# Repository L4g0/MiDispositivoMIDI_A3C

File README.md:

# BanaNut Electronics
Hi! We are BanaNut Electronics and we develop software and hardware for Arduino with educational purposes. Feel free to visit us in out social networks:
* Instagram: https://www.instagram.com/bananutelectronics
* Twitter: https://twitter.com/bn_electronics
* Facebook: https://www.facebook.com/bananutelectronics
* Tindie: https://www.tindie.com

# MiDispositivoMIDI_A3C
We are proud to present the MiDispositivoMIDI revA3C ([what is that?](https://github.com/bananutelectronics/MiDispositivoMIDI_A3C/wiki), which is the latest version we have out in the market. You can buy it in our webpage or in tindie. In this repository you will find documentation about the controller and code. If you know how to code and you want to colaborate with the project, feel free to do it. If you don't, here you will find a bunch of codes that you just will need to upload to your controller, simple as that.

# Important
You will need the following libraries to make the code work: MIDI USB and Adafruit NeoPixel
* https://github.com/arduino-libraries/MIDIUSB
* https://github.com/adafruit/Adafruit_NeoPixel

We also recommend using the Arduino Sketch to make the programming. Remember to select "Arduino Leonardo" as target board.

# Media
* https://www.youtube.com/watch?v=3QnzLwpbpRE&t
* https://www.youtube.com/watch?v=8WFfShg-0Dk
* https://www.youtube.com/watch?v=2y8fhmTmedI
* https://www.youtube.com/watch?v=TsuVpFoLFyI

# General information
* MiDispositivoMIDI is the latest version of our controller.
* It can act as any other MIDI device. There is no need to convert from serial to MIDI.
* Have 16 pad buttons in a 4x4 matrix.
* Have 2 lateral buttons.
* Have RGB leds with 256 levels of intensity of each color.
* Micro USB conection.
* Dimensions of 10x10 cm.

# Documentation
Check the wiki section for further information.

# Hardware License
<br /><span xmlns:dct="http://purl.org/dc/terms/" property="dct:title">MiDispositivoMIDI</span> by <a xmlns:cc="http://creativecommons.org/ns#" href="www.bananutelectronics.com" property="cc:attributionName" rel="cc:attributionURL">Alvaro Lopez & Pablo de Miguel Morales</a> is licensed under a <a rel="license" href="http://creativecommons.org/licenses/by-nc-sa/4.0/">Creative Commons Attribution-NonCommercial-ShareAlike 4.0 International License</a>.<br />

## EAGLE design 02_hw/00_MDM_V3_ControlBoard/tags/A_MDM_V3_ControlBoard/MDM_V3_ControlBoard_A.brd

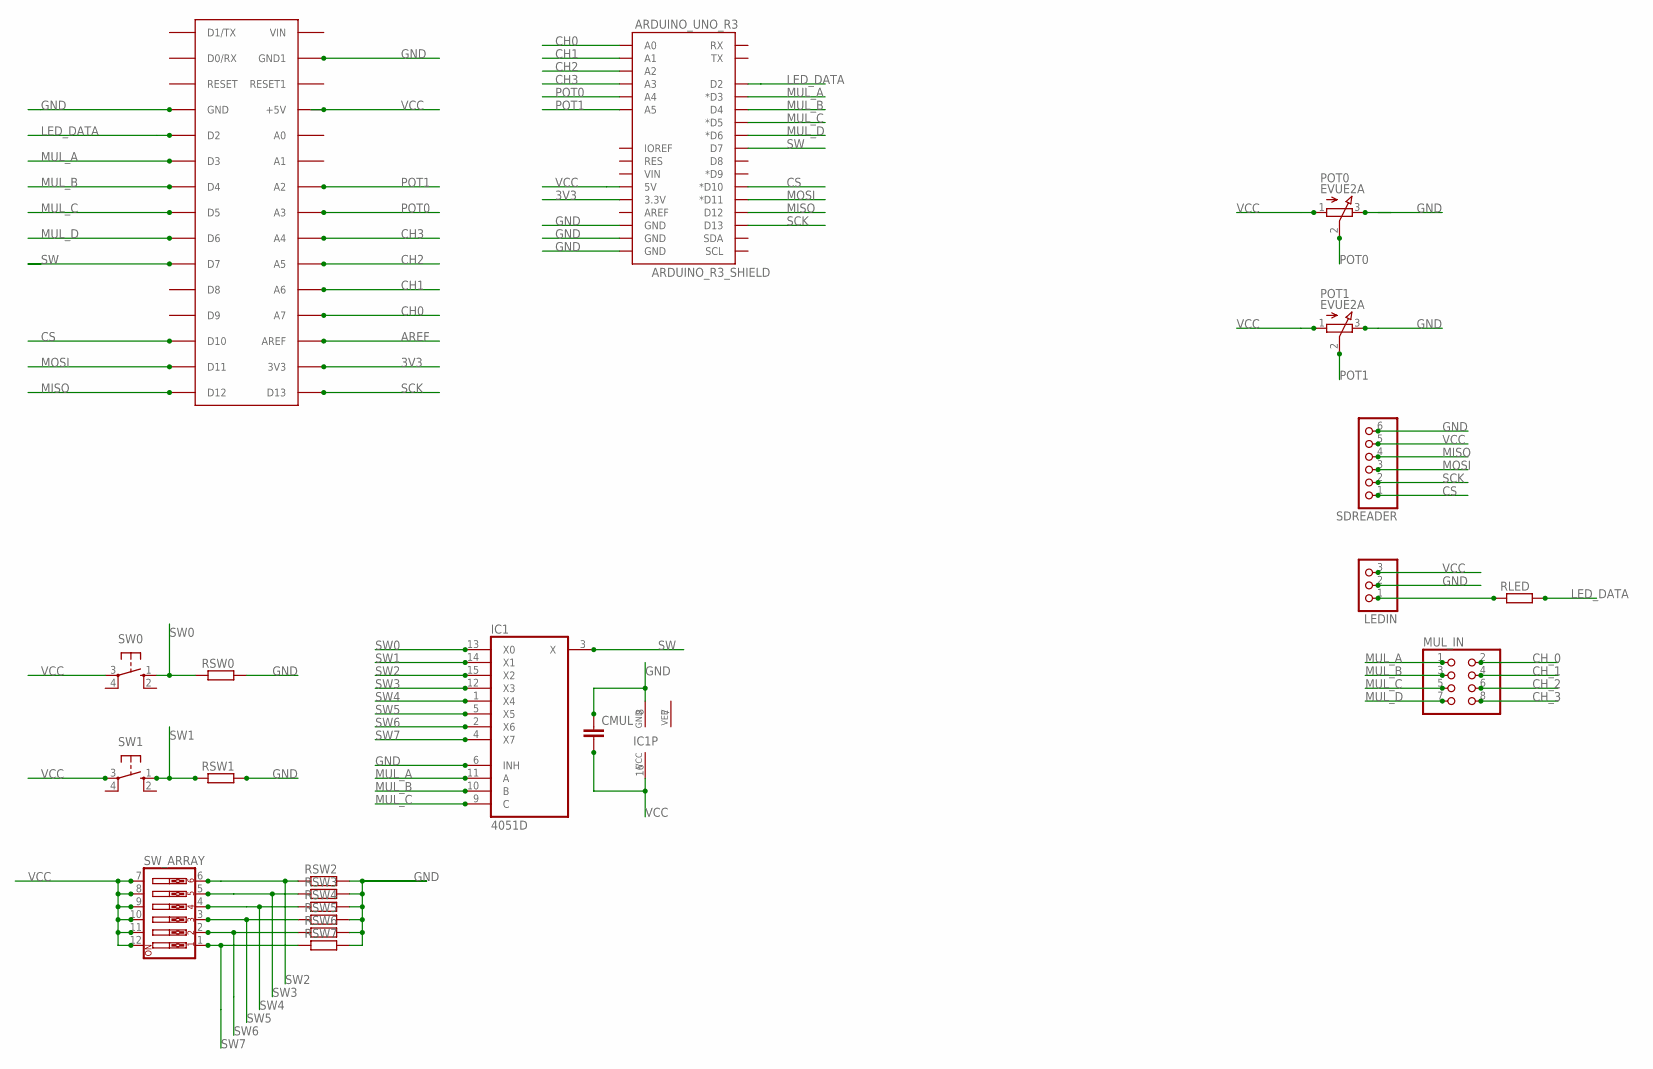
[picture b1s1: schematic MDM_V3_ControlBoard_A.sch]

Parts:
ARDUINO_NANO: ARDUINONANO; PDIP-32
ARDUINO_UNO_R3: ARDUINO_R3_SHIELD; UNO_R3_SHIELD
CMUL: C-EUC1206; C1206
IC1: 4051D; SO16
LEDIN: PINHD-1X3; 1X03
MUL_IN: PINHD-2X4; 2X04
POT0, POT1: EVUE2A; EVUE
RLED: R-EU_M1206; M1206
RSW0, RSW1, RSW2, RSW3, RSW4, RSW5, RSW6, RSW7: R-EU_M1206; M1206
SDREADER: PINHD-1X6; 1X06
SW0, SW1: 10-XX; B3F-10XX
SW_ARRAY: SW_DIP-6; EDG-06

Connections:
3V3: ARDUINO_NANO.3V3, ARDUINO_UNO_R3.3.3V
AREF: ARDUINO_NANO.AREF
CH0: ARDUINO_NANO.A7, ARDUINO_UNO_R3.A0
CH1: ARDUINO_NANO.A6, ARDUINO_UNO_R3.A1
CH2: ARDUINO_NANO.A5, ARDUINO_UNO_R3.A2
CH3: ARDUINO_NANO.A4, ARDUINO_UNO_R3.A3
CH_0: MUL_IN.2
CH_1: MUL_IN.4
CH_2: MUL_IN.6
CH_3: MUL_IN.8
CS: ARDUINO_NANO.D10, ARDUINO_UNO_R3.D10 (*D10), SDREADER.1
GND: ARDUINO_NANO.GND, ARDUINO_NANO.GND1, ARDUINO_UNO_R3.GND@0 (GND), ARDUINO_UNO_R3.GND@1 (GND), ARDUINO_UNO_R3.GND@2 (GND), CMUL.1, IC1.6 (INH), IC1.8 (GND), LEDIN.2, POT0.3 (E), POT1.3 (E), RSW0.2, RSW1.2, RSW2.2, RSW3.2, RSW4.2, RSW5.2, RSW6.2, RSW7.2, SDREADER.6
LED_DATA: ARDUINO_NANO.D2, ARDUINO_UNO_R3.D2, RLED.2
MISO: ARDUINO_NANO.D12, ARDUINO_UNO_R3.D12, SDREADER.4
MOSI: ARDUINO_NANO.D11, ARDUINO_UNO_R3.D11 (*D11), SDREADER.3
MUL_A: ARDUINO_NANO.D3, ARDUINO_UNO_R3.D3 (*D3), IC1.11 (A), MUL_IN.1
MUL_B: ARDUINO_NANO.D4, ARDUINO_UNO_R3.D4, IC1.10 (B), MUL_IN.3
MUL_C: ARDUINO_NANO.D5, ARDUINO_UNO_R3.D5 (*D5), IC1.9 (C), MUL_IN.5
MUL_D: ARDUINO_NANO.D6, ARDUINO_UNO_R3.D6 (*D6), MUL_IN.7
unnamed: LEDIN.1, RLED.1
POT0: ARDUINO_NANO.A3, ARDUINO_UNO_R3.A4, POT0.2 (S)
POT1: ARDUINO_NANO.A2, ARDUINO_UNO_R3.A5, POT1.2 (S)
SCK: ARDUINO_NANO.D13, ARDUINO_UNO_R3.D13, SDREADER.2
SW: ARDUINO_NANO.D7, ARDUINO_UNO_R3.D7, IC1.3 (X)
SW0: IC1.13 (X0), RSW0.1, SW0.1 (S)
SW1: IC1.14 (X1), RSW1.1, SW1.1 (S)
SW2: IC1.15 (X2), RSW2.1, SW_ARRAY.6
SW3: IC1.12 (X3), RSW3.1, SW_ARRAY.5
SW4: IC1.1 (X4), RSW4.1, SW_ARRAY.4
SW5: IC1.5 (X5), RSW5.1, SW_ARRAY.3
SW6: IC1.2 (X6), RSW6.1, SW_ARRAY.2
SW7: IC1.4 (X7), RSW7.1, SW_ARRAY.1
VCC: ARDUINO_NANO.+5V, ARDUINO_UNO_R3.5V, CMUL.2, IC1.16 (VCC), LEDIN.3, POT0.1 (A), POT1.1 (A), SDREADER.5, SW0.3, SW1.3, SW_ARRAY.7, SW_ARRAY.8, SW_ARRAY.9, SW_ARRAY.10, SW_ARRAY.11, SW_ARRAY.12
VEE: IC1.7 (VEE)

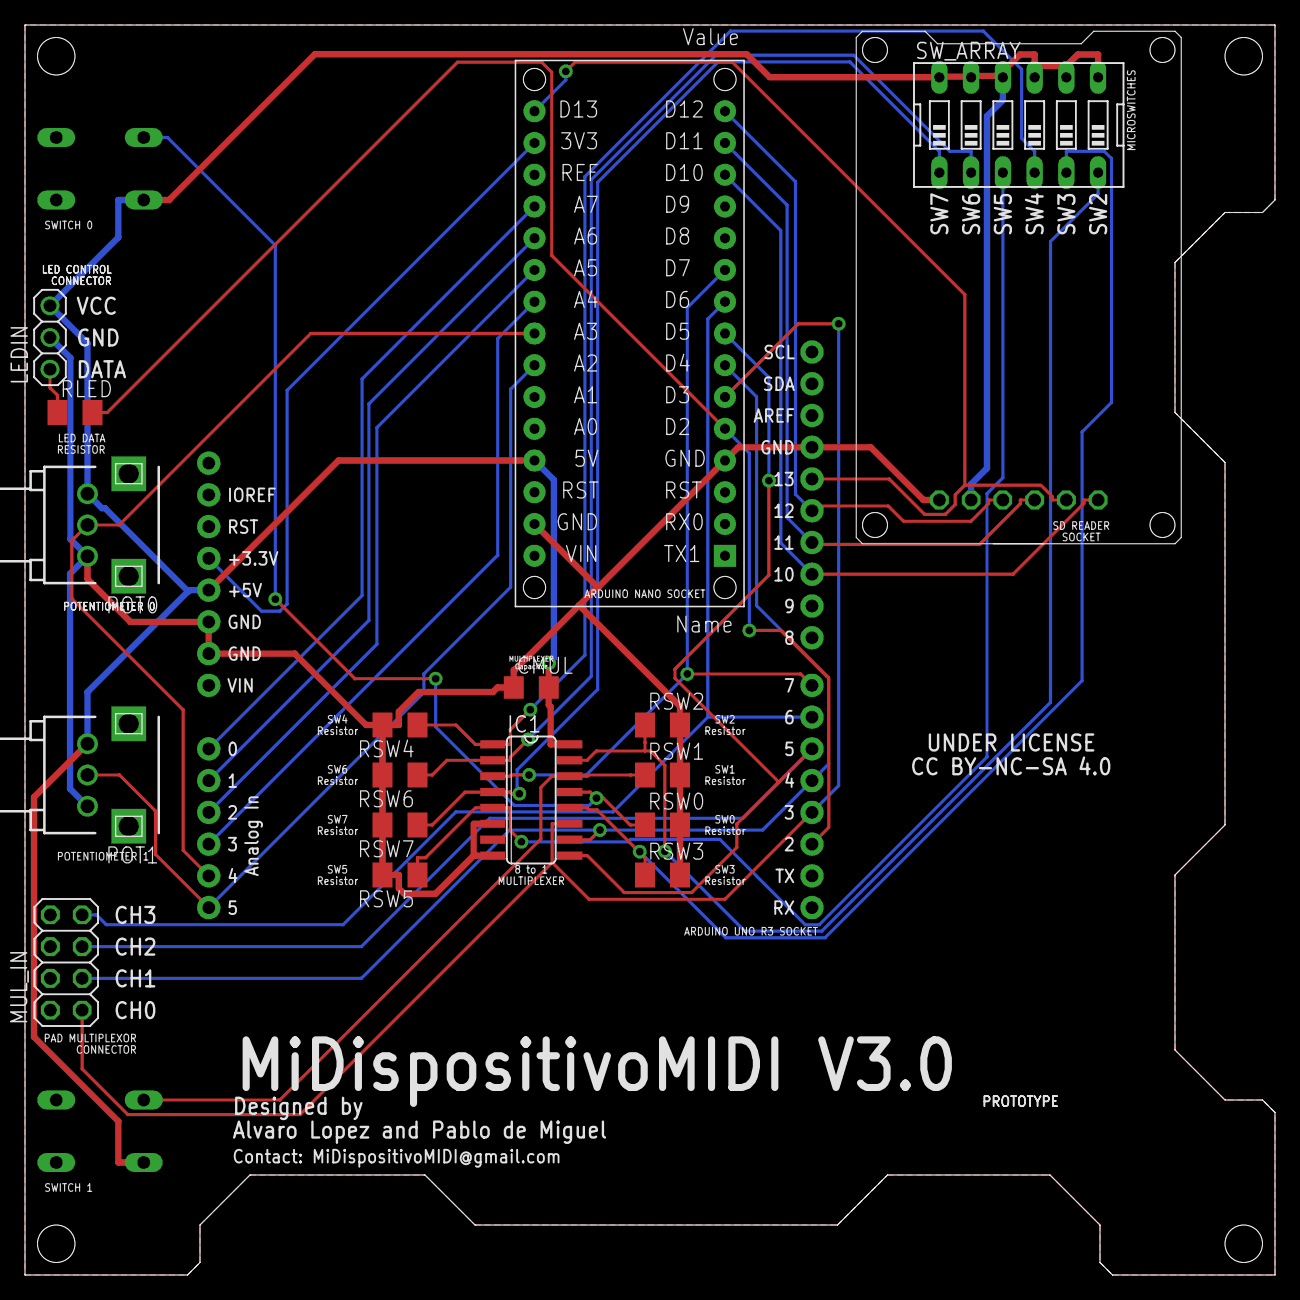
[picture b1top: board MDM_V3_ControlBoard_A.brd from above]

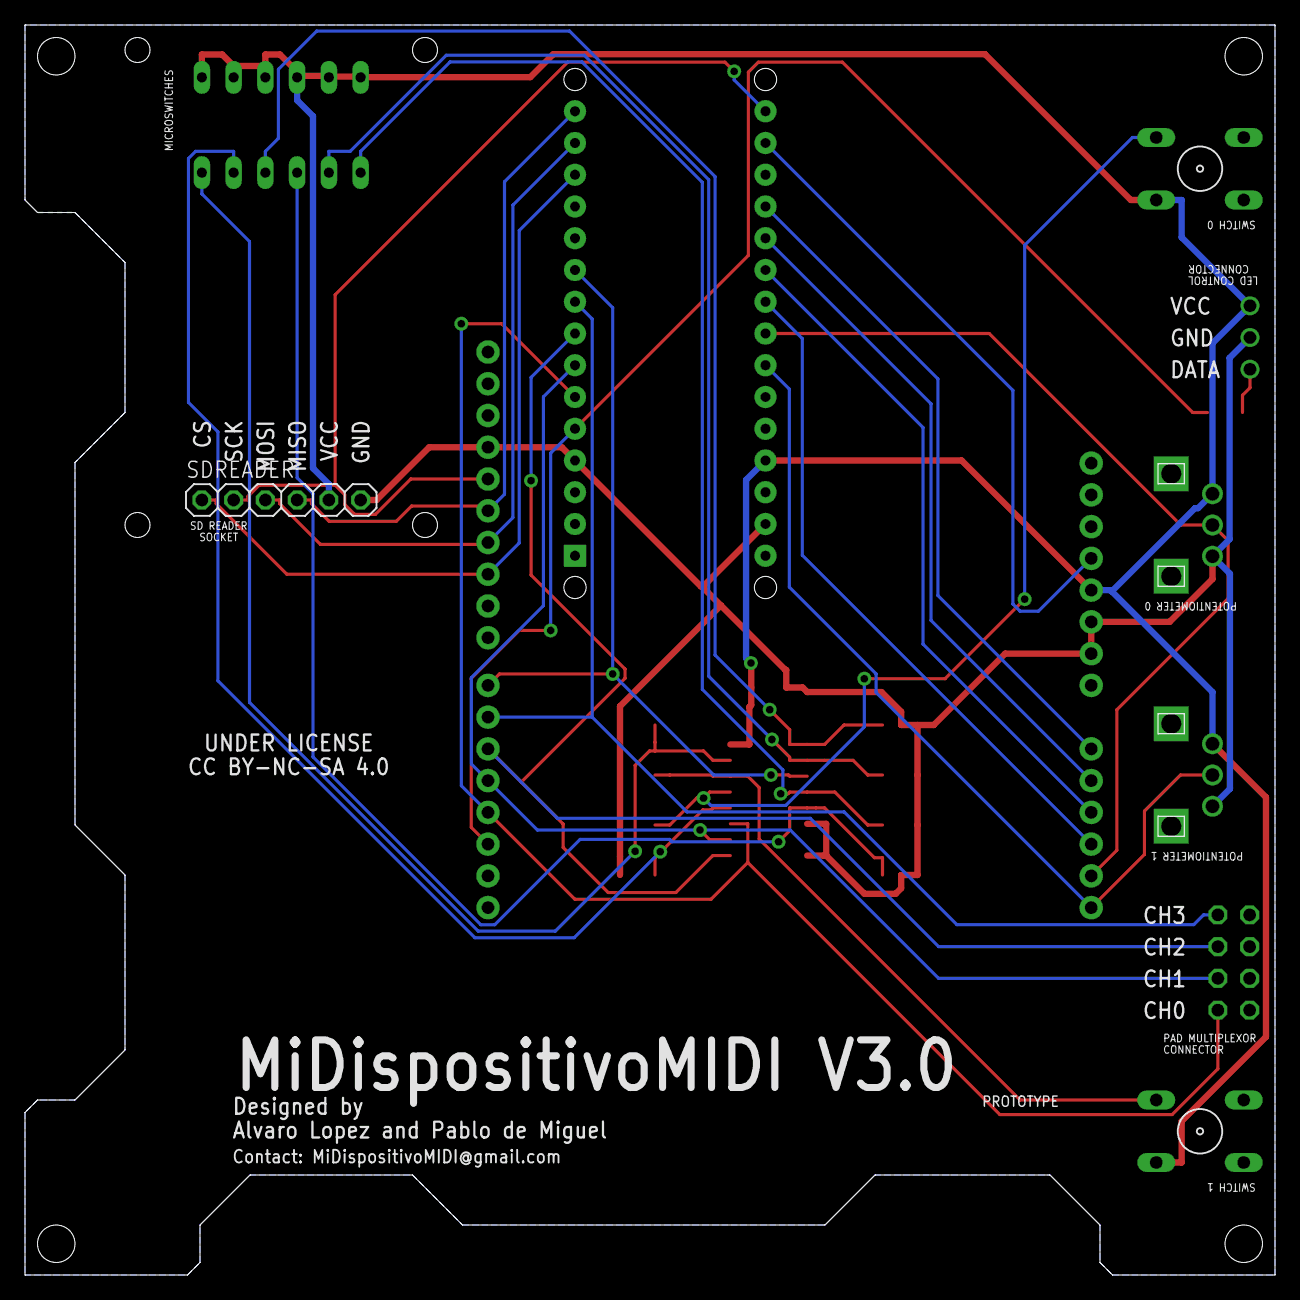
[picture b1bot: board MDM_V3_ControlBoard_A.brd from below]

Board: 2 copper layers, 100.0 x 100.0 mm, 21 parts (3 on the bottom side), 28 nets.

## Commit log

2017-02-17 RevA3C
2017-03-09 Wiki Images Uploaded
2017-03-16 Wiki Images
    Wiki Images Updates
2018-03-03 Uploading code. Main code is from Bananut's unreleased fw. Features added by Bananut: color selection by palette, more control by constants, reorganiced stuff... Upgrades by UC3Music: working scale c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
2018-03-03 New Colors, Drums Teamplate and Solved Bugs
    With this version of the code some "bugs" are solved, we have more colors and if we select the white template (in the color selection) a drum template is showing in order to see the mapping better...
    Also, when you change the scale a blue light will blink in order "to see" the change of the scale.

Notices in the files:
02_hw/00_MDM_V3_ControlBoard/tags/A_MDM_V3_ControlBoard/MDM_V3_ControlBoard_A.brd:
UNDER LICENSE
CC BY-NC-SA 4.0
parts and their libraries:
SparkFun-Boards: Licensing: Creative Commons ShareAlike 4.0 International - https://creativecommons.org/licenses/by-sa/4.0
